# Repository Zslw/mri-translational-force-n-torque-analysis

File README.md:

# MRI Safety Thesis -- Analysis Code & Data

**Author:** Daniel Juarez Luna  
**Institution:** Creighton University, MSc Medical Physics  
**Advisor:** Michael G. Nichols, PhD  
**Thesis title:** Magnetically Induced Forces on Temporary Epicardial Leads: Experimental Device Development and Clinical Testing  
**Status:** Completed -- pending committee approval for formal submission (April 2026)

---

## Overview

This repository contains all Jupyter notebooks, raw experimental data, and generated
figures supporting the above MSc thesis. The work quantifies magnetically induced
translational forces and torques on retained post-surgical epicardial pacing leads
in the static field of a 3T MRI scanner, using three custom non-magnetic fixtures
developed and validated in the lab before clinical deployment at CHI Health
CUMC-Bergan Mercy, Omaha NE.

The clinical analysis pipeline follows ASTM F2052-15 (Standard Test Method for
Measurement of Magnetically Induced Displacement Force on Medical Devices in the
MR Environment) and draws conceptually from ASTM F2213-17 (Standard Test Method
for Measurement of Magnetically Induced Torque).

All code, data, and notebooks live inside the JupyterLab/ subfolder. This mirrors
the local working directory structure. Navigate there first.

---

## A note on notebook organization

Each experimental folder contains a mix of notebooks reflecting the actual
development process -- early attempts, working drafts, and final analyses often
sit side by side. The notes below identify which notebooks produced the reported
results and figures, and which are working history kept for transparency.

Figure files are currently stored alongside notebooks within each folder. Moving
figures into dedicated subfolders is noted as a future cleanup task and will be
done after formal thesis submission. Any such commit will be documentation only
and will not affect the analysis code or data.

---

## Repository Structure

All paths below are relative to JupyterLab/.

---

### BfieldSIM/ -- Magnetic field simulation and solenoid mapping

| Notebook | Role |
|---|---|
| FieldMapping.ipynb | PRIMARY MODEL. Finite solenoid simulation using the Biot-Savart approach. Produces the background chapter field profile figure and the chi/rho scaling table. |
| BfieldAnalysis.ipynb | PRIMARY ANALYSIS. Step-by-step processing of gaussmeter data from the lab solenoid. Produces results chapter figures (B vs z, dB/dz, B times grad B). |
| Bfield.ipynb | First attempt at solenoid simulation. Superseded by FieldMapping.ipynb, kept for reference. |
| BfieldMapping.ipynb | First attempt at visualizing solenoid field data. Superseded by BfieldAnalysis.ipynb, kept for reference. |

Thesis figures: combined_figure41.png and combined_gradients42.png correspond to
Figures 4.1 and 4.2 in the thesis. Other .png files in this folder are intermediate
or exploratory outputs.

Raw data: BfieldMapData/ contains gaussmeter CSV files (gm2_set_5 through
gm2_set_10) and landmark Excel files used for spatial registration.

---

### Translational/ -- Lab translational force experiment

| Notebook | Role |
|---|---|
| FitSus.ipynb | PRIMARY. Full pipeline: susceptibility fitting, tan(alpha) vs B times grad B, uncertainty propagation, chi_m extraction. Referenced in thesis methodology Chapter 3 and results Chapter 4. |
| AppendixB.ipynb | Lab report appendix submitted for PHY797 DIR (Direct Independent Research), written alongside the FitSus work during that course. Not part of the thesis itself. |
| Mini Project exploration/ | Early vector potential exploration in Mathematica and notebook form. Background reading, not part of reported results. |

Raw data: RawMeasurments.csv, RawMeasurmentsMagneticfield.csv,
RawMeasurmentsMagneticfieldGrad.csv  
Processed data: cleanData.csv, cleanDatawstdsem.csv  
Publication figures: Assests/ folder contains Residuals_Plot.png and related
final figures  
3D print file: smaller-optimized-honycombCard for MRI.stl -- hexagonal mesh basket
used to hold test objects on the pendulum fixture (Figure 3.9 in thesis)

---

### Torque/ -- Torque sensor development and lab measurements

#### Torque/Calibration/

This folder has no single primary notebook. Reported content is spread across
multiple notebooks reflecting how the calibration developed iteratively.

| Notebook | Role |
|---|---|
| Torque-plots.ipynb | First attempt at calibration curves. Glass and plastic sensor curves from this notebook appear in Appendix E of the thesis. |
| Torque-plots-Copy1.ipynb | Contains the final calibration slope for the aluminum sensor, noise level measurement, and the reported detection limit. Closest to a primary notebook in this folder. |
| Upright-Torque-plots.ipynb | First attempt at upright sensor orientation -- exploratory only, nothing reported. |
| Upright-Torque-plots-Copy1.ipynb | Tests and visualization attempts for upright orientation data. |
| Upright-Torque-plots-Copy2.ipynb | Better visualization pass. Contains the 1/r fit and sensor position optimization plots that appear in Appendix E. |
| data_compiler.ipynb | Compiles raw .dat run files into merged dataframes for the calibration notebooks. |

Raw data: dataTorque/ (first calibration session) and New_dataTorque/ (updated
session). Each contains per-rod, per-orientation CSV files.  
Key output figures: inverseRfitFr.png, powerFitFr.png, table_min_detect_mass_alt.png

#### Torque/MRIForces/

| Notebook | Role |
|---|---|
| Torque_Analysis_v2.ipynb | PRIMARY. Structured final analysis of lab torque measurements. Covers Helmholtz coil trials (long rod) and neodymium magnet trials (short rod), fits the tau proportional to B squared dependence, and produces all reported torque figures and summary CSVs. |
| Torque_again.ipynb | Second attempt focused on what was measurable. Some material went to a poster presentation but nothing carried into the thesis. Kept for reference. |
| Torque Presentation.ipynb | First attempt -- exploratory fits and interpretation. Superseded, kept for reference. |

Raw data: Helmholtz long-rod and short-rod trial CSVs, neodymium short-rod trial
CSVs, and angle-dependent measurement files.  
Publication figures: fig_torque_LR.png (Figure 4.12), fig_torque_SR_neo.png
(Figure 4.13)  
Output data: torque_mindetectable.csv, torque_results_summary.csv

---

### ClinicalData/ -- Primary clinical analysis

Real magnetic flux density measurements taken at the bore entrance of the 3T
Siemens Magnetom scanner at CUMC-Bergan Mercy, Omaha NE. Grid coordinate labels
(00, A3, A6, D3, G3, G6) refer to positions on the custom PVC mapping fixture
described in thesis Chapter 3. Analysis follows ASTM F2052-15.

#### How the three notebooks connect

ClinicalBfieldAnalysis.ipynb and Translational_F2052.ipynb are upstream notebooks
that each handle one half of the F2052-15 analysis -- field characterization and
pendulum deflection respectively. Both notebooks contain partial prediction attempts
that are intentionally incomplete on their own. Each saves its results to a .pkl
file. MRI_F2052_Comparison.ipynb loads both .pkl files and produces the full
compliance report, allowable gradient extrapolation, and cross-coordinate
predictions.

To reproduce: run ClinicalBfieldAnalysis.ipynb and Translational_F2052.ipynb
first (in either order), then run MRI_F2052_Comparison.ipynb.

```
ClinicalBfieldAnalysis.ipynb          Translational_F2052.ipynb
   (MappingBField/)                      (TranslationalExperiment/)
         |                                         |
         |  outputs/clinical_summary.pkl           |  outputs/mean_results.pkl
         +------------------+-----------------------+
                            |
                            v
                 MRI_F2052_Comparison.ipynb
                  (cross-analysis and F2052-15 report)
```

#### MappingBField/

| Notebook | Role |
|---|---|
| ClinicalBfieldAnalysis.ipynb | PRIMARY. Full multi-coordinate pipeline: load CSVs, remove outliers, crop static ends, split sub-runs, convert time to position, compute B and dB/dz and B times grad B via central differences, produce summary table. Saves outputs/clinical_summary.pkl for downstream use. |
| G6ClinicalBfieldAnalysis.ipynb | Earlier G6-only analysis. Superseded by the full pipeline above, kept for reference. |
| GaussmeterReps.ipynb | Repeatability study. Work in progress -- being continued by junior lab members. |

Raw data: DataCollectionFolderMRIProject/ contains 15 CSV files, one per coordinate
per pass direction (forward and backward). Also archived as .7z.  
Per-coordinate figures: betterPlots/ contains B, dB/dz, and B times grad B vs
position for each grid point.  
Summary figures: allCoords_betterPlots/ contains summary_B.png, summary_dBdz.png,
summary_BgradB.png, and summary_vertical_overlay_clean.png.

#### TranslationalExperiment/

| Notebook | Role |
|---|---|
| Translational_F2052.ipynb | PRIMARY. ASTM F2052-15 pendulum protocol: parse CSV, compute alpha and tan(alpha), average across trials, compute force ratio FR, run Appendix X3 extrapolation. Saves outputs/mean_results.pkl for downstream use. |

Raw data: Translational Data taken around G6 - Sheet1.csv -- hand-recorded pendulum
displacement measurements for Ti coil, Medtronic STREAMLINE 6492 unipolar epicardial
lead, Ti straight rod, and 316L stainless steel.  
Publication figures: F2052_FR_vs_position_pub.png (Figure 4.7),
F2052_max_FR_comparison_pub.png (Figure 4.8)

#### ClinicalData/ root level

| Notebook | Role |
|---|---|
| MRI_F2052_Comparison.ipynb | PRIMARY. Links both upstream pipelines. Loads .pkl outputs, identifies test location per ASTM F2052-15 section 8.1, extracts measured B0 and grad B from the field map, runs Appendix X3 extrapolation for all devices at 1.5T and 3.0T, produces consolidated compliance report. |
| Map_translational.ipynb | Earlier combined notebook that attempted to do everything in one place. Superseded by the split pipeline above, kept for reference. |

Publication figures: comparison_FR_per_coordinate_pub.png (Figure 4.10),
comparison_allowable_gradient_pub.png (Figure 4.9)

---

### MapField/ -- Gaussmeter sampling rate raw data

Raw .csv and .dat files from the sampling rate characterization experiment
described in FindSampleRateMagFieldMap.ipynb at the JupyterLab/ root level.
This tested the gaussmeter acquisition rate under low-flux conditions. Result:
0.25 s sampling interval was used in the clinical session; subsequent analysis
suggested 0.5 s would have been more appropriate. This is discussed in thesis
Chapter 3.

---

### Poster1/ -- Early learning material

Brights Thesis/RescaleFigures.ipynb was created at the start of the project to
reproduce figures from a prior student's RF heating thesis while learning Python
and Jupyter. Included for completeness, not part of reported results.

---

### SmallestTorquecalcs.xlsx

Spreadsheet backing the sample calculations in thesis Appendix B.3 (Smallest
measurable torque on fixture). Shows worked numerical examples for the cantilever
beam strain equations and detection limit estimation. This is not a final result --
the reported minimum detectable torque comes from the calibration notebook.

---

## Full Repository Tree

```
mri-translational-force-n-torque-analysis/
├── README.md
├── LICENSE
├── .gitignore
└── JupyterLab/
    ├── .gitignore
    ├── FindSampleRateMagFieldMap.ipynb        # Gaussmeter sampling rate test
    ├── SmallestTorquecalcs.xlsx               # Appendix B.3 sample calculations
    ├── MapField/                              # Raw data for sampling rate test
    │   ├── FindSampleRate.csv
    │   ├── FindSampleRate2.csv
    │   ├── FindSampleRate2_run1.dat
    │   ├── FindSampleRate2_run2.dat
    │   ├── FindSampleRate2_run3.dat
    │   ├── FindSampleRate2_run4.dat
    │   ├── FindSampleRate2_run5.dat
    │   ├── FindSampleRate3.csv
    │   ├── FindSampleRate3_run1.dat
    │   ├── FindSampleRate3_run2.dat
    │   ├── FindSampleRate_run1.dat
    │   ├── FindSampleRate_run2.dat
    │   ├── FindSampleRate_run3.dat
    │   └── FindSampleRate_run4.dat
    ├── BfieldSIM/
    │   ├── FieldMapping.ipynb                 # PRIMARY MODEL: solenoid simulation
    │   ├── BfieldAnalysis.ipynb               # PRIMARY ANALYSIS: solenoid data
    │   ├── Bfield.ipynb                       # First attempt (reference)
    │   ├── BfieldMapping.ipynb                # First attempt (reference)
    │   ├── combined_figure41.png              # Thesis Figure 4.1
    │   ├── combined_gradients42.png           # Thesis Figure 4.2
    │   ├── [intermediate figures]
    │   └── BfieldMapData/
    │       ├── gm2_set_5.csv
    │       ├── gm2_set_6.csv
    │       ├── gm2_set_7.csv
    │       ├── gm2_set_8.csv
    │       ├── gm2_set_8_landmarked.csv
    │       ├── gm2_set_9.csv
    │       ├── gm2_set_9_landmarked.csv
    │       ├── gm2_set_10.csv
    │       ├── landmarked.xlsx
    │       └── landmarks.xlsx
    ├── Translational/
    │   ├── FitSus.ipynb                       # PRIMARY: susceptibility fit
    │   ├── AppendixB.ipynb                    # PHY797 DIR lab report appendix
    │   ├── RawMeasurments.csv
    │   ├── RawMeasurmentsMagneticfield.csv
    │   ├── RawMeasurmentsMagneticfieldGrad.csv
    │   ├── cleanData.csv
    │   ├── cleanDatawstdsem.csv
    │   ├── curve_fit_plot.png
    │   ├── linear_fit.png
    │   ├── FitSus.html
    │   ├── FitSus_files/
    │   ├── smaller-optimized-honycombCard for MRI.stl
    │   ├── Assests/                           # Publication figures
    │   │   ├── Residuals_Plot.png
    │   │   ├── Angle_vs_Field.png
    │   │   ├── Displacement_vs_Current.png
    │   │   ├── Force_vs_Field.png
    │   │   ├── Uncertainty_Propagation_Plot.png
    │   │   └── magField_behavior_SI.png
    │   └── Mini Project exploration/
    │       ├── MRI_Safety_Phase1_VectorPotential.ipynb
    │       └── demo4.nb
    ├── Torque/
    │   ├── Calibration/
    │   │   ├── Torque-plots.ipynb             # Glass and plastic curves (Appendix E)
    │   │   ├── Torque-plots-Copy1.ipynb       # Aluminum sensor final calibration
    │   │   ├── Upright-Torque-plots.ipynb     # First upright attempt (reference)
    │   │   ├── Upright-Torque-plots-Copy1.ipynb
    │   │   ├── Upright-Torque-plots-Copy2.ipynb  # 1/r fit and position plots (Appendix E)
    │   │   ├── data_compiler.ipynb
    │   │   ├── df_merged.csv
    │   │   ├── compiled_torque_july4.dat
    │   │   ├── compiled_torque_july11.dat
    │   │   ├── compiled_upright_torque_july4.dat
    │   │   ├── compiled_upright_torque_july11.dat
    │   │   ├── inverseRfitFr.png
    │   │   ├── powerFitFr.png
    │   │   ├── table_min_detect_mass_alt.png
    │   │   ├── rod_characteristics_table.png
    │   │   ├── rod_characteristics_table.tex
    │   │   ├── 1stTrials_50_90.png
    │   │   ├── dataTorque/                    # First calibration session
    │   │   ├── dataTorque.zip
    │   │   ├── New_dataTorque/                # Updated calibration session
    │   │   └── New_dataTorque.zip
    │   └── MRIForces/
    │       ├── Torque_Analysis_v2.ipynb       # PRIMARY: final torque analysis
    │       ├── Torque_again.ipynb             # Second attempt (poster, reference)
    │       ├── Torque Presentation.ipynb      # First attempt (reference)
    │       ├── Helmholtz-Torque-Data1-73025.csv
    │       ├── Helmholtz-Torque-Data1-80425.csv
    │       ├── Helmholtz-Torque-Data2LR-73025.csv
    │       ├── Helmholtz-Torque-DataLR-73125.csv
    │       ├── TorqueMeasurement_SR_120825.csv
    │       ├── TorqueMeasurement_SR_120825_cont.csv
    │       ├── TorqueMeasurement_SR_120825_all.csv
    │       ├── torqueangles_0to45.csv
    │       ├── torqueangles_30to150.csv
    │       ├── fig_torque_LR.png              # Thesis Figure 4.12
    │       ├── fig_torque_SR_neo.png          # Thesis Figure 4.13
    │       ├── torque_SR_neoFits.png
    │       ├── torque_LR_fits.png
    │       ├── torque_SR_helm.png
    │       ├── torque_angle_check.png
    │       ├── torque_clinical_projection.png
    │       ├── fig_torque_projection.png
    │       ├── torque_mindetectable.csv
    │       └── torque_results_summary.csv
    ├── ClinicalData/
    │   ├── MRI_F2052_Comparison.ipynb         # PRIMARY: cross-analysis and report
    │   ├── Map_translational.ipynb            # Earlier combined notebook (reference)
    │   ├── comparison_FR_per_coordinate.png
    │   ├── comparison_FR_per_coordinate_pub.png   # Thesis Figure 4.10
    │   ├── comparison_allowable_gradient.png
    │   ├── comparison_allowable_gradient_pub.png  # Thesis Figure 4.9
    │   ├── MappingBField/
    │   │   ├── ClinicalBfieldAnalysis.ipynb   # PRIMARY: full field mapping pipeline
    │   │   ├── G6ClinicalBfieldAnalysis.ipynb # Earlier G6-only (reference)
    │   │   ├── GaussmeterReps.ipynb           # Repeatability study (WIP)
    │   │   ├── repeated_flux_analysis.png
    │   │   ├── DataCollectionFolderMRIProject/    # Raw CSVs: 00, A3, A6, D3, G3, G6
    │   │   ├── DataCollectionFolderMRIProject.7z
    │   │   ├── betterPlots/                   # Per-coordinate B, dB/dz, B times grad B
    │   │   ├── allCoords_betterPlots/         # Summary figures across all coordinates
    │   │   │   ├── summary_B.png
    │   │   │   ├── summary_dBdz.png
    │   │   │   ├── summary_BgradB.png
    │   │   │   └── summary_vertical_overlay_clean.png
    │   │   ├── G6betterPlots/                 # Earlier G6-only figures (reference)
    │   │   └── outputs/
    │   │       └── clinical_summary.pkl
    │   └── TranslationalExperiment/
    │       ├── Translational_F2052.ipynb      # PRIMARY: F2052-15 pendulum protocol
    │       ├── Translational Data taken around G6 - Sheet1.csv
    │       ├── F2052_FR_vs_position.png
    │       ├── F2052_FR_vs_position_pub.png   # Thesis Figure 4.7
    │       ├── F2052_max_FR_comparison.png
    │       ├── F2052_max_FR_comparison_pub.png    # Thesis Figure 4.8
    │       └── outputs/
    │           ├── mean_results.pkl
    │           └── translational_summary.pkl
    └── Poster1/
        └── Brights Thesis/
            └── RescaleFigures.ipynb           # Early learning notebook (reference)
```

---

## Dependencies

```
pandas  numpy  scipy  matplotlib
```

```bash
pip install pandas numpy scipy matplotlib
```

No additional libraries required. Inter-notebook data exchange uses Python's
built-in pickle module. No parquet engine needed.

---

## Appendix F -- Repository Archive Record

This section is the timestamp record referenced in Appendix F of the thesis. It
documents the state of this repository at the time of thesis completion. Because
this repository remains publicly editable after submission, this printed record
serves as the authoritative reference for what existed at the time of publication.
Any content added after commit 8435c9b is supplementary and not part of the
reported work.

| Field | Value |
|---|---|
| Repository | https://github.com/Zslw/mri-translational-force-n-torque-analysis |
| Branch | main |
| Thesis sync commit | 8435c9b |
| Commit message | Final thesis sync: updated notebooks, publication figures, and appendix calculations |
| Date of sync | April 23, 2026 |
| Scanner | Siemens Magnetom 3T at CHI Health CUMC-Bergan Mercy, Omaha NE |
| Device tested | Medtronic STREAMLINE 6492 unipolar temporary epicardial lead |
| Standards followed | ASTM F2052-15, ASTM F2213-17 |
| Primary result | Force ratio FR = 0.093 (alpha = 5.32 degrees) -- passes F2052-15 threshold (FR less than 1.0) |

All notebooks, raw data CSVs, and publication figures present at commit 8435c9b
represent the complete computational record of the experimental work reported in
the thesis. No analysis code changes are anticipated after this point. Any future
commits will be documentation or formatting only.

---

## Citing This Work

Juarez Luna, D. (2026). Magnetically Induced Forces on Temporary Epicardial Leads:
Experimental Device Development and Clinical Testing. MSc Medical Physics,
Creighton University.  
Code and data: https://github.com/Zslw/mri-translational-force-n-torque-analysis

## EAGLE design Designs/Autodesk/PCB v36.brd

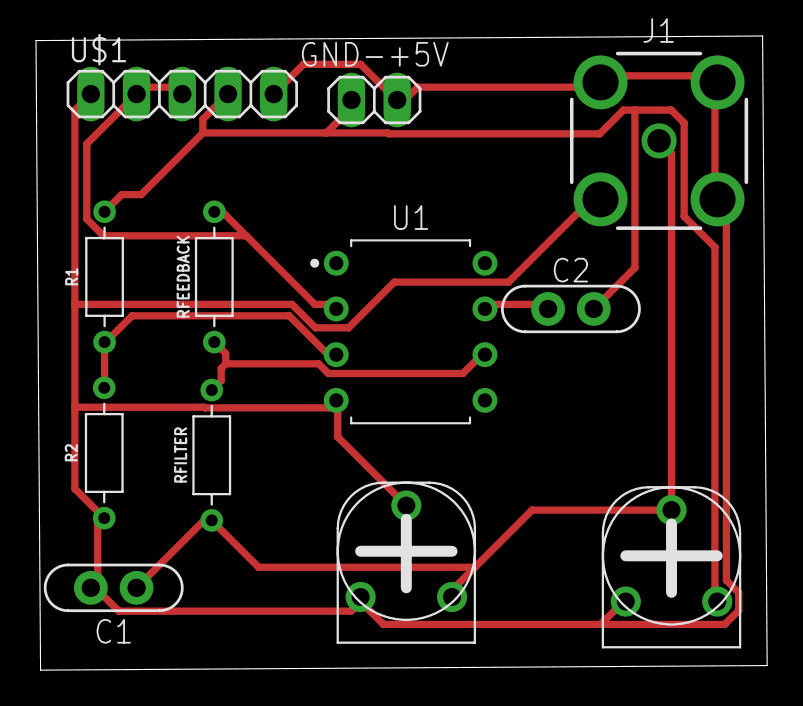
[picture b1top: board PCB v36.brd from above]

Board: 2 copper layers, 40.6 x 35.2 mm, 12 parts (0 on the bottom side), 7 nets.

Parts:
C1, C2: 10u; CAP-THRU-2.54MM
GND-+5V: PINHD-1X2; 1X02
J1: 60711002241501
R1, R2: 1k; RESAD724W46L381D178B
R3, R4: HA-06-SM065
RFEEDBACK: 24M; RESAD724W46L381D178B
RFILTER: 47k; RESAD724W46L381D178B
U1: LM741; DIP826W53P254L959H508Q8B
U$1: PINHD-1X05_1X05M; 1X05

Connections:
+5V: C2.2, GND-+5V.1, R1.2, R3.3, U$1.4
AGND: C1.2, GND-+5V.2, J1.2, J1.3, J1.4, J1.5, R2.1, R3.1, R4.1, R4.2, U1.4, U$1.1, U$1.5
unnamed: C2.1, U1.7
unnamed: C1.1, J1.1, R3.2, R4.3, RFILTER.2
unnamed: RFEEDBACK.2, RFILTER.1, U1.6
unnamed: R1.1, R2.2, U1.3
unnamed: RFEEDBACK.1, U1.2, U$1.2, U$1.3

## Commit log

2026-02-23 Initial commit: MRI safety thesis analysis code and data
2026-02-23 minor edits on the readme
2026-02-23 Fix README tree formatting
2026-03-10 Add B-field mapping analysis notebooks and figures
    BfieldSIM:
    - BfieldAnalysis.ipynb: B vs z, dB/dz and B·dB/dz for solenoid
    scan (center, SW edge, east edge); forward/backward split at
    peak B; central difference gradient; summary table
    - Updated gradB.png and new BvsTime, BvsZ, gradBvsZ, BgradBvsZ plots
    ClinicalData:
2026-03-11 Reorganize into MappingBField/ and TranslationalExperiment/ subfolders
    - Move ClinicalBfieldAnalysis and data into MappingBField/
    - Move Translational experiment notebooks and data into TranslationalExperiment/
    - Add MRI_F2052_Comparison.ipynb linking both analyses
    - Add comparison plots (FR per coordinate, allowable gradient)
    - Remove old flat ClinicalData layout and G6-only notebooks
2026-03-11 Update README: accurate structure from git ls-tree, document F2052-15 pipeline
2026-03-16 Add Torque_Analysis_v2: consolidated torque analysis and clinical projection
    - Add Torque_Analysis_v2.ipynb: consolidates Helmholtz (SR) and neodymium (LR)
    torque trials, fits torque vs B-field, validates angle dependence, and projects
    to 3T clinical setting
    - Add output figures: fig_torque_SR_neo, fig_torque_LR, fig_torque_projection,
    torque_SR_helm, torque_SR_neoFits, torque_LR_fits, torque_angle_check,
    torque_clinical_projection
2026-04-10 Added stl file for 3d printing of mesh and changes on plots for readability
2026-04-10 added stl for real
2026-04-10 moved stl and added to readme
2026-04-23 Final thesis sync: updated notebooks, publication figures, and appendix calculations
    - Resized and reformatted figures across BfieldSIM, ClinicalData, Torque, Translational
    - Added combined thesis figures (Fig 4.1, 4.2 equivalents)
    - Added _pub figures: FR vs position, max FR comparison, allowable gradient
    - Added vertical overlay summary for all coordinates
    - Added G6 three-panel figure
    - Added SmallestTorquecalcs.xlsx (Appendix B.3 sample calculations)
2026-04-23 moved find sample rate data at same level at is notebook
2026-04-23 README: full thesis documentation, corrected notebook roles, full tree, Appendix F archive record
2026-05-23 tweaked plots for publishing and minor details
2026-05-27 just in case final edits
2026-05-30 remove private files from public repo

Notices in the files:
parts and their libraries:
Wurth_Connectors_WR-BNC: Copyright: Würth Elektronik
